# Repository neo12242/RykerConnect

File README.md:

> **Hardware testing status:** I have not tested this project on physical hardware yet. I am still working on my hardware. Software and simulator checks do not establish that the physical hardware works.

# RykerConnect

A motorcycle companion app, ESP32-S3 display system, and hardware-free simulator, based on [JanB97/RykerConnect](https://github.com/JanB97/RykerConnect). This fork brings the Android software expansion and the revised JLCPCB carrier designs together. It is a prototype project, not a validated vehicle accessory.

## What is included

- **Android app:** Dashboard, Bluetooth connection tools, GPS ride recording and summaries, trip maps/replay/charts, photos, fuel and maintenance records, vehicle profiles, themes, home-screen widgets, and local backup/restore.
- **ESP simulator:** A virtual BLE peripheral connected through Android Emulator/netsim, with two browser-rendered OLED panels, settings, sensor controls, failure scenarios, and a guided ride.
- **Firmware:** PlatformIO sources for the revised boards, including the REV05 PCF8563 clock and BME280 sensor support.
- **Hardware:** Native KiCad designs, local libraries, Gerbers, JLCPCB BOM/placement files, wiring instructions, and prototype acceptance procedures.
- **Optional DadRides integration:** Publishing stays built into the Android APK and is disabled by default. The [DadRides website/API](https://github.com/neo12242/DadRides) lives in a separate repository. There is no separate plugin APK, and the app works without the website.

Phone and ESP editions now share ownership spending, modification tracking and service tools. Ride recovery, shared libraries and Wear OS controls are also included; see [current application updates](docs/CURRENT-FEATURES.md). Personal deployment notes, backups, credentials and ride data are excluded from source publication.

## Start here

| Goal | Guide |
|---|---|
| Try the app and virtual displays without electronics | [Simulator setup and use](Simulator/README.md) |
| Build/install the Android app | [Android setup](docs/ANDROID.md) |
| Learn the app's features | [User guide](docs/USER-GUIDE.md) |
| Select a PCB and find the JLCPCB upload files | [Hardware guide](Hardware/README.md) |
| Build firmware | [Firmware guide](Firmware/README.md) |
| Understand this fork's changes and limitations | [Changes](docs/CHANGES.md) |
| Develop from the maintained checkout and run baseline checks | [Development and validation](docs/DEVELOPMENT.md) |
| Configure the optional public ride site | [DadRides](https://github.com/neo12242/DadRides) |

## Visual tour

These development screenshots illustrate the app and simulator. Some show earlier navigation layouts. Demo routes and guided rides are synthetic. Click an image to view it at full size.

| Android dashboard | Trip maps and replay | Simulator sensor controls |
|---|---|---|
|  |  |  |
| Ride information, music, and navigation in one dashboard, with tabs for connection tools, trips, garage, and settings. | Explore a synthetic demonstration ride. The map marks its start and finish, while replay follows the recorded timeline. Gaps remain visible instead of implying continuous GPS coverage. | Toggle virtual sensors and test missing or stale readings. This screen models the earlier DS3231 clock; REV05 hardware uses PCF8563 and requires separate physical testing. |
| [App user guide](docs/USER-GUIDE.md) | [Ride features](docs/USER-GUIDE.md#rides) | [Simulator setup and controls](Simulator/README.md) |

### Try it without hardware

The guided demo previews music, navigation, sensor readings, and ride progress. Playback controls let you start, reset, and change speed without recording a real trip.

See [foldable presentation setup](Simulator/README.md#optional-foldable-presentation).

### REV05C-12V carrier board

KiCad top-layer artwork for the cost-reduced carrier prototype, showing module sockets, battery holder, power circuitry, and peripheral connections. **This is design artwork—not a photograph of assembled or tested hardware.**

See the [hardware guide](Hardware/README.md) for revision selection, matched JLCPCB upload files, separate purchases, and power precautions.

## Quick start: Windows simulator

The first run requires Android Studio/SDK, a Google APIs x86_64 emulator named `RykerConnect_Pixel_7`, Python 3.13, a built debug APK, and the simulator's Python environment. See the [full guide](Simulator/README.md) before running these commands from the repository root:

```powershell
cd Android
.\gradlew.bat assembleCompanionDebug assemblePhoneDebug
cd ..
py -3.13 -m venv Simulator/.venv
.\Simulator\.venv\Scripts\python.exe -m pip install -r Simulator/requirements.txt
& '.\Start RykerConnect Demo.cmd'
```

In the app, open **Connect**, select **RykerConnect-MainUnit**, and pair with the simulator's public test PIN **123456**. The OLED preview opens at <http://127.0.0.1:8876/>. Use **Settings**, **Test scenarios**, and the **I2C test bench** to explore. No physical ESP or Bluetooth dongle is needed for the virtual connection. An intercom is not simulated.

The simulator models protocol/display behavior; it does **not** execute ESP firmware or emulate electrical hardware. Its RTC controls model the earlier DS3231 behavior, while REV05 hardware uses PCF8563. Neither validates the other electrically.

## Hardware status

The latest cost-reduced accessory-power prototype is **REV05C-12V**. **REV05-USB** is a separate USB/regulated-5V option. Use a variant's Gerbers, BOM and CPL together. Do not mix revisions. Read [power selection and bench acceptance](Hardware/REV05C-12V/POWER-AND-TEST.md) before applying power. USB and external power must not be connected together with J8 closed.

JLCPCB placement/model alignment, through-hole assembly acceptance, physical boot, sensor wiring, thermal behavior, enclosure fit and vehicle testing remain pending. Past pricing/stock observations are dated snapshots, not current quotes. The development board, displays, sensor, battery and mating cables are separate purchases.

## Privacy and configuration

The published source excludes local pairing keys, owner keys, SDK paths, app-data backups, ride/receipt exports, logs and development caches. Local setup creates new private files; keep them ignored. Never upload `Simulator/bonds.json`, DadRides `.dev.vars`/`owner-local.txt`, signing keys, or app backups. Backups are not encrypted and may contain locations, vehicle details and original photo metadata.

DadRides uploads only after enabling/configuring the integration and preparing a public copy. Review route trimming and selected photos before publishing. Endpoint trimming is not a guarantee of anonymity. The site does not need a Cloudflare account token in the app.

## Repository layout

`Android/`, `Simulator/`, `Firmware/RykerConnect-REV05/`, and `Hardware/REV05C-12V/` are the current entry points. Older local revisions remain for reference and generation dependencies. Upstream `AndroidApp/`, `Software/`, `Firmware/MainUnit_ESP32S3-REV01/`, `Hardware/KiCad/` and `CAD/` are retained for provenance; their APKs/firmware and enclosure are not the updated release. Build the current source instead.

## Attribution and license

Original project by [JanB97](https://github.com/JanB97), with upstream contributors and notices preserved. This fork retains the upstream [GPL-3.0 license](LICENSE). The [original README](docs/UPSTREAM-README.md) records upstream limitations. Dependencies and vendor documents retain their respective notices and licenses.

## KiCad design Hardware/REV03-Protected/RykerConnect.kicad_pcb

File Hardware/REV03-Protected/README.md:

> Historical revision: see [the hardware index](../README.md) for current options. Physical testing is pending.

# RykerConnect REV03 — protected accessory-input prototype

**Use this revision for the new prototype.** It supersedes the REV02 manufacturing set for the ignition-switched 12V accessory installation. The source Downloads project and the previous REV02 package remain unchanged. This is a completed design/export package; no physical board has been assembled or tested.

## JLCPCB files

Upload these together, without mixing revisions:

1. `manufacturing/Gerbers.zip` — fabrication layers and plated/non-plated drills.
2. `manufacturing/BOM.csv` — **44 fitted components in 31 part groups**, all with LCSC catalog codes.
3. `manufacturing/CPL.csv` — **32 top-side and 12 bottom-side placements**.

Select an assembly service supporting both sides, the through-hole J1 and USB mechanical tabs. J1 is intentionally included in the CPL. Confirm stock, any preorder/Global Sourcing, and actual placement models before ordering. A catalog code is not a stock reservation or assembly acceptance. Use the Gerbers.zip above for fabrication, not the complete delivery archive.

The enclosure must clear the newly populated underside. Reserve roughly 3mm below the PCB for these components and verify the actual enclosure and manufacturer models before fabrication. The board outline and mounting-hole positions are preserved. This revision may cost more to assemble because it uses both sides.

## What changed

The accessory path is now:

**Fused, switched accessory 12V → J1 → transient suppressors/input capacitors → U6 electronic protection → original diode OR-ing → original 3.3V converter.**

- U6, TI **TPS26600PWPR**, adds reverse-input blocking, programmable overvoltage disconnect, startup slew control and approximately 1A overcurrent protection. MODE is open, selecting the auto-retry circuit-breaker behavior; SHDN uses its internal bias.
- R7/R8/R9 form a 120k/20k/10k divider: nominal **17.85V overvoltage cutoff**, **16.5V recovery**, and **5.95V undervoltage startup threshold**. Low voltage during engine cranking can shut the unit down and restart it; uninterrupted crank operation is not claimed.
- R10 is 12k for nominal 1A protection. C16 is 10nF for approximately a 1ms output ramp at 12V. The current limit is a protection threshold, not a new 1A external accessory output.
- D2 **SMBJ33A** and D4 **SMBJ18A** form an asymmetric TVS pair, connected anode-to-anode. The lower negative clamp accounts for the charged output capacitor and the chip's input-to-output voltage limit. Neither diode is the bidirectional `CA` version.
- C14/C17 provide 2uF nominal, 100V-rated input capacitance. C15 adds local output capacitance. D3 **B140-13-F**, cathode to protected output, limits negative output excursions.
- U6's RTN and exposed pad use an **isolated bottom copper island**. They are deliberately not tied to system GND. The custom footprint follows TI's PWP0016A land drawing, with a segmented exposed-pad paste pattern. There are no through-board thermal vias in this island; temperature at the real load must be checked.
- The protection circuit is on the bottom, preserving the original outline and front-side component locations. Two local ground returns were provided, and decorative bottom artwork was moved away from the new circuit. Original author attribution remains.
- The USB input remains behind its original diode OR-ing path. No firmware-controlled power sequencing or new Android feature was required.

## Installation and sensor

the project owner confirmed **ignition-switched accessory 12V** and approximately **one foot / 30cm** of sensor cable. Use a properly fused accessory branch and verify its connector polarity and wire rating. The electronic protection does not protect upstream wiring or a fault in the input TVS itself. Do not replace the vehicle's fuse with a larger value to address a fault. The unit normally powers off with the accessory supply; a connected USB supply can still power it.

Keep the external sensor as an assembled [Adafruit BME280 STEMMA QT module, product 2652](https://www.adafruit.com/product/2652), connected directly to J5 at 100kHz I2C. No extender is fitted for the initial one-foot run. Confirm reliable operation with the actual cable and vehicle electrical loads.

| J5 pin | Signal |
|---|---|
| 1 | GND |
| 2 | +3.3V |
| 3 | SDA, GPIO8 |
| 4 | SCL, GPIO18 |

Use a correctly wired JST SH/STEMMA QT cable. Power off before connection, and never put vehicle 12V or 5V on J5. Locate the sensor away from engine/electronics heat and sunlight, inside a ventilated splash-protected enclosure. Temperature, humidity and absolute pressure are measurements; they remain separate from GPS weather forecasts. A BMP280 is not a humidity-capable replacement.

The battery holder is assembled on the PCB; the CR2032 cell, OLED, external sensor module, cables, media remote and enclosure are separate items. Turnkey PCB assembly does not automatically include these items or firmware programming.

## Validation performed

- KiCad 10.0.6: **zero configured DRC violations, zero unconnected items, zero schematic parity issues, zero ERC violations**. This does not mean all optional KiCad rules were enabled.
- BOM/CPL sets match all 44 fitted components. The source netlist independently confirms that J1 feeds U6, the protected output feeds D1, the TVS diodes share only their anodes, and RTN is separate from GND.
- DC corner calculations include independent pin leakage and resistor tolerances. With 1% resistors the calculated cutoff is 17.20–18.75V. A wider 2.5% resistor-error envelope gives 16.73–19.28V, preserving margin above normal 16V operation and below the existing 25V capacitor rating. These are static calculations, not measured transient overshoot.
- Only new protection nets were imported from local Freerouting output. Existing signal and USB routing were not imported or optimized by that tool. The detailed native checks are the acceptance results; intermediate router logs are diagnostic.
- Original source hashes, board outline and retained component positions are checked. The preserved REV02 software is reused; it was previously built successfully with 32 Android unit tests passing. It was not reflashed or physically retested for this revision.

Reports, native placements, schematic/assembly PDFs, calculations and routing provenance are in `validation`. Purchasing identities and sources are in `selected-parts.json`.

## Prototype acceptance still required

This circuit targets normal 9–16V accessory operation, reverse connection at -16V, overvoltage disconnect for a **suppressed load dump up to 35V**, and short transients within the TVS ratings. It is **not qualified for a full unsuppressed alternator load dump**, and is not an ISO 7637/16750-certified automotive assembly. The protection chip is an industrial-rated part. Actual temperature, pulse energy, source impedance, DC-bias capacitance and PCB overshoot must be tested.

Before committing an assembly order, review:

1. JLCPCB stock/process acceptance and model alignment for every part, especially U6/D2/D3/D4 and the bottom-side rotation convention. U6 pin 1 must agree with the board marker. D2/D4 cathode polarity is essential.
2. J1/J2 mechanical fit, the exact SOG320132A OLED variant, and underside/enclosure clearance.
3. The actual accessory branch fuse and cable ratings.

Then test the assembled prototype on a protected, current-limited bench supply before connecting it to the vehicle:

1. Inspect soldering, isolated RTN, polarity and input/3.3V continuity.
2. Verify normal supply startup, soft start, overvoltage disconnect/recovery and undervoltage behavior. Apply controlled reverse-polarity tests with current limiting and no alternate grounded cables that could bypass the test path.
3. Verify overload/short-circuit auto-retry and temperature at the intended load. Recheck the regulator's local ground return.
4. Test the specified transient waveforms with suitable equipment; verify voltage at both U6 and the downstream converter, not just at J1.
5. Verify the OLED, USB, Bluetooth, RTC and environmental readings; confirm unavailable/stale readings and recovery. Finally test engine-start and vehicle electrical-noise behavior.

## Placement conventions and software

CPL coordinates share the KiCad auxiliary origin on both sides. Existing assembler adjustments are retained: J1 centroid offset (-1.5mm X, -2.53mm Y), U1 rotation +180 degrees and U2 rotation -90 degrees. New bottom parts use the native KiCad orientation as the model-preview starting point. These are not a substitute for JLCPCB's actual placement preview. DNP C1/C2/JP1 and off-board Q1 stay excluded; test pads, mounting holes and artwork stay excluded.

The included `software` files are the previously built REV02/N8 firmware and Android debug APK, reused unchanged because GPIOs, memory variant and sensor protocol are unchanged. Use the `RykerConnect_REV02` PlatformIO environment from the included firmware source for a complete first-board upload. `firmware.bin` alone is only the application image; do not flash it at address zero. The APK is not installed by this package. Earlier simulator-only trip/navigation/weather display extensions remain separate from this physical firmware.

## Rebuild

Keep this directory beside `REV02-Corrected`, which is the preserved input. Run `build_schematic.py` with regular Python, then `build_board.py`, `import_routing.py` and `finish_board.py` with KiCad's bundled Python; run `check_calculations.py` and `export_release.py` with regular Python. Run `finish_board.py` once per fresh board build. The saved `validation/protection.ses` supplies the reviewed routing, so reproducing the delivered design does not require downloading an autorouter.

For intentional rerouting, `prepare_routing.py` fixes existing routes in DSN and defines new net widths. Local Freerouting 2.4.1 was run with analytics, GUI, server, fanout and optimizer disabled. `import_routing.py` imports only the eight protection nets and rejects component movements by ignoring placement data. Reinspect and revalidate any rerouted result; the current finishing adjustments apply to the delivered geometry only.

References: [TI TPS2660 datasheet and reference circuit](https://www.ti.com/lit/ds/symlink/tps2660.pdf), [Littelfuse SMBJ datasheet](https://m.littelfuse.com/~/media/electronics/datasheets/tvs_diodes/littelfuse_tvs_diode_smbj_datasheet.pdf.pdf), [Freerouting CLI](https://github.com/freerouting/freerouting/blob/v2.4.1/docs/command_line_arguments.md). Per-part catalog links are recorded with the BOM identities.

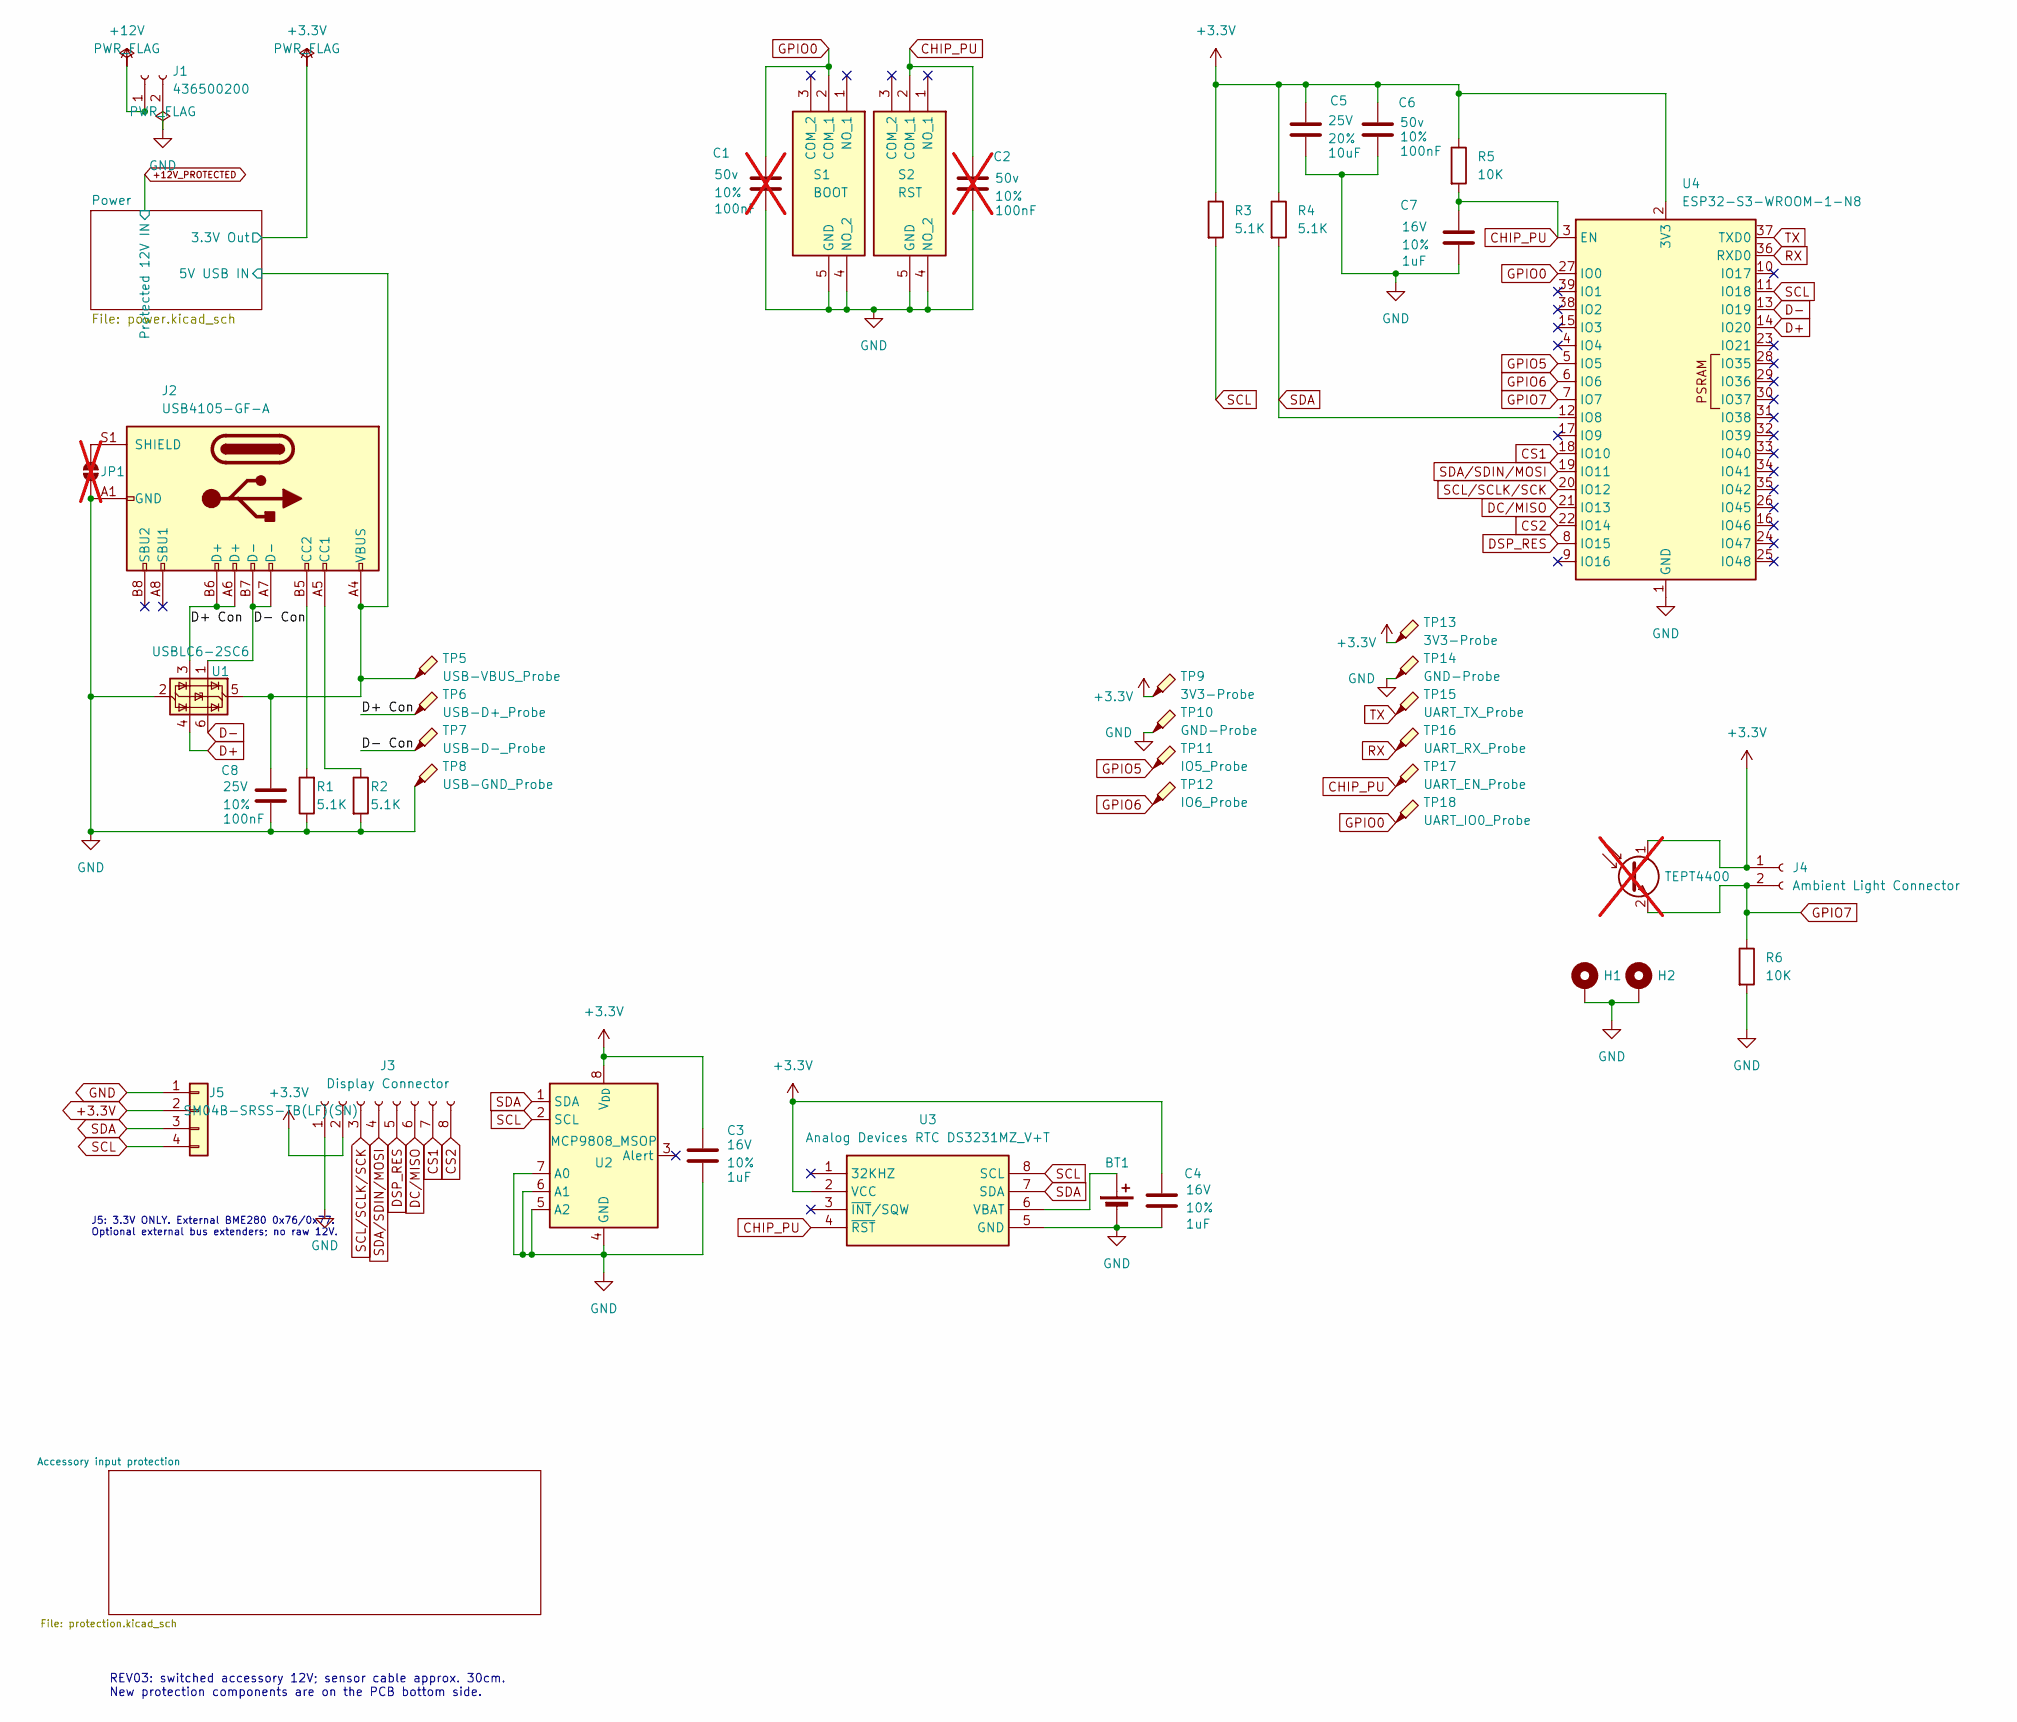
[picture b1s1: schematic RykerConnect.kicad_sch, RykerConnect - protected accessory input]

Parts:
BT1: Holders Linx CR2032; BT1_BATHLD001; MPN BAT-HLD-001; LCSC C7501066
C1: 100nF; C1_C_0603_1608Metric_Pad1.08x0.95mm_HandSolder; Voltage 50v; Tolerance 10%; not fitted
C2: 100nF; C2_C_0603_1608Metric_Pad1.08x0.95mm_HandSolder; Voltage 50v; Tolerance 10%; not fitted
C3: 1uF; C3_C_0603_1608Metric_Pad1.08x0.95mm_HandSolder; Voltage 16V; Tolerance 10%; MPN CL10B105KO8NNNC; LCSC C59782
C4: 1uF; C4_C_0603_1608Metric_Pad1.08x0.95mm_HandSolder; Voltage 16V; Tolerance 10%; MPN CL10B105KO8NNNC; LCSC C59782
C5: 10uF; C5_C_0603_1608Metric_Pad1.08x0.95mm_HandSolder; Voltage 25V; Tolerance 20%; MPN C1608X5R1E106M080AC; LCSC C2168289
C6: 100nF; C6_C_0603_1608Metric_Pad1.08x0.95mm_HandSolder; Voltage 50v; Tolerance 10%; MPN C0603C104K5RAC7082; LCSC C1882722
C7: 1uF; C7_C_0603_1608Metric_Pad1.08x0.95mm_HandSolder; Voltage 16V; Tolerance 10%; MPN CL10B105KO8NNNC; LCSC C59782
C8: 100nF; C8_C_0603_1608Metric_Pad1.08x0.95mm_HandSolder; Voltage 25V; Tolerance 10%; MPN C0603C104K3RACTU; LCSC C2167527
H1: MountingHole_Pad; H1_MountingHole_2.2mm_M2_ISO14580_Pad_TopBottom
H2: MountingHole_Pad; H2_MountingHole_2.2mm_M2_ISO14580_Pad_TopBottom
J1: 436500200; J1_43650-02_00,01,02_; MPN 436500200; LCSC C192562
J2: USB4105-GF-A; J2_USB_C_Receptacle_GCT_USB4105-xx-A_16P_TopMnt_Horizontal; MPN USB4105-GF-A; LCSC C3020560
J3: Display Connector; J3_JST_SH_SM08B-SRSS-TB_1x08-1MP_P1.00mm_Horizontal; MPN SM08B-SRSS-TB(LF)(SN); LCSC C160407
J4: Ambient Light Connector; J4_JST_SH_SM02B-SRSS-TB_1x02-1MP_P1.00mm_Horizontal; MPN SM02B-SRSS-TB(LF)(SN); LCSC C160402
J5: SM04B-SRSS-TB(LF)(SN); J5_JST_SH_SM04B-SRSS-TB_1x04-1MP_P1.00mm_Horizontal; MPN SM04B-SRSS-TB(LF)(SN); LCSC C160404
JP1: SolderJumper_2_Open; JP1_R_0603_1608Metric_Pad0.98x0.95mm_HandSolder; not fitted
Q1: TEPT4400; LED_D3.0mm_Clear; not fitted
R1: 5.1K; R1_R_0805_2012Metric_Pad1.20x1.40mm_HandSolder; MPN RS73F2ARTTD5101D; LCSC C5890991
R2: 5.1K; R2_R_0805_2012Metric_Pad1.20x1.40mm_HandSolder; MPN RS73F2ARTTD5101D; LCSC C5890991
R3: 5.1K; R3_R_0805_2012Metric_Pad1.20x1.40mm_HandSolder; MPN RS73F2ARTTD5101D; LCSC C5890991
R4: 5.1K; R4_R_0805_2012Metric_Pad1.20x1.40mm_HandSolder; MPN RS73F2ARTTD5101D; LCSC C5890991
R5: 10K; R5_R_0805_2012Metric_Pad1.20x1.40mm_HandSolder; Tolerance 1%; MPN CRGP0805F10K; LCSC C2074940
R6: 10K; R6_R_0805_2012Metric_Pad1.20x1.40mm_HandSolder; MPN CRGP0805F10K; LCSC C2074940
S1: BOOT; S1_435451019820; Mouser Part Number 710-435451019820
S2: RST; S2_435451019820; Mouser Part Number 710-435451019820
TP5: USB-VBUS_Probe; TP5_TestPoint_Pad_D1.0mm
TP6: USB-D+_Probe; TP6_TestPoint_Pad_D1.0mm
TP7: USB-D-_Probe; TP7_TestPoint_Pad_D1.0mm
TP8: USB-GND_Probe; TP8_TestPoint_Pad_D1.0mm
TP9: 3V3-Probe; TP9_TestPoint_Pad_D2.0mm
TP10: GND-Probe; TP10_TestPoint_Pad_D2.0mm
TP11: IO5_Probe; TP11_TestPoint_Pad_D2.0mm
TP12: IO6_Probe; TP12_TestPoint_Pad_D2.0mm
TP13: 3V3-Probe; TP13_TestPoint_Pad_D1.5mm
TP14: GND-Probe; TP14_TestPoint_Pad_D1.5mm
TP15: UART_TX_Probe; TP15_TestPoint_Pad_D1.5mm
TP16: UART_RX_Probe; TP16_TestPoint_Pad_D1.5mm
TP17: UART_EN_Probe; TP17_TestPoint_Pad_D1.5mm
TP18: UART_IO0_Probe; TP18_TestPoint_Pad_D1.5mm
U1: USBLC6-2SC6; U1_SOT-23-6; MPN USBLC6-2SC6; LCSC C7519
U2: MCP9808_MSOP; U2_MSOP-8_3x3mm_P0.65mm; MPN MCP9808T-E/MS; LCSC C129490
U3: Analog Devices RTC DS3231MZ_V+T; U3_SOIC127P600X175-8N; Mouser Part Number 700-DS3231MZ/V+T
U4: ESP32-S3-WROOM-1-N8; U4_ESP32-S3-WROOM-1; MPN ESP32-S3-WROOM-1-N8; LCSC C2913198

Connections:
+3.3V: C3.1, C4.1, C5.1, C6.1, J3.2, J4.1, J5.2, Q1.1 (C), R3.1, R4.1, R5.1, TP9.1 (1_1), TP13.1 (1_1), U2.8 (V_{DD}), U3.2 (VCC), U4.2 (3V3); also elsewhere on the board
+12V: J1.1; also elsewhere on the board
/D+ Con: J2.A6 (D+), J2.B6 (D+), TP6.1 (1_1), U1.3 (I/O2)
/D- Con: J2.A7 (D-), J2.B7 (D-), TP7.1 (1_1), U1.1 (I/O1)
/Power/5V USB IN: C8.1, J2.A4 (VBUS), J2.A9 (VBUS), J2.B4 (VBUS), J2.B9 (VBUS), TP5.1 (1_1), U1.5 (VBUS); also elsewhere on the board
CHIP_PU: C2.1, C7.1, R5.2, S2.2 (COM_1), TP17.1 (1_1), U3.4 (~RST), U4.3 (EN)
CS1: J3.7, U4.18 (IO10)
CS2: J3.8, U4.22 (IO14)
D+: U1.4 (I/O2), U4.14 (IO20)
D-: U1.6 (I/O1), U4.13 (IO19)
DC/MISO: J3.6, U4.21 (IO13)
DSP_RES: J3.5, U4.8 (IO15)
GND: BT1.2 (-), C1.2, C2.2, C3.2, C4.2, C5.2, C6.2, C7.2, C8.2, H1.1 (1_1), H2.1 (1_1), J1.2, J2.A1 (GND), J2.A12 (GND), J2.B1 (GND), J2.B12 (GND), J3.1, J5.1, J5.MP (Mounting anchors), JP1.1 (A), R1.1, R2.2, R6.2, S1.4 (NO_2), S1.5 (GND), S2.4 (NO_2), S2.5 (GND), TP8.1 (1_1), TP10.1 (1_1), TP14.1 (1_1), U1.2 (GND), U2.4 (GND), U2.5 (A2), U2.6 (A1), U2.7 (A0), U3.5 (GND), U4.1 (GND), U4.40 (GND); also elsewhere on the board
GPIO0: C1.1, S1.2 (COM_1), TP18.1 (1_1), U4.27 (IO0)
GPIO5: TP11.1 (1_1), U4.5 (IO5)
GPIO6: TP12.1 (1_1), U4.6 (IO6)
GPIO7: J4.2, Q1.2 (E), R6.1, U4.7 (IO7)
unnamed: BT1.1 (+), U3.6 (VBAT)
unnamed: J2.A5 (CC1), R2.1
unnamed: J2.B5 (CC2), R1.2
unnamed: J2.S1 (SHIELD), JP1.2 (B)
RX: TP16.1 (1_1), U4.36 (RXD0)
SCL: J5.4, R3.2, U2.2 (SCL), U3.8 (SCL), U4.11 (IO18)
SCL/SCLK/SCK: J3.3, U4.20 (IO12)
SDA: J5.3, R4.2, U2.1 (SDA), U3.7 (SDA), U4.12 (IO8)
SDA/SDIN/MOSI: J3.4, U4.19 (IO11)
TX: TP15.1 (1_1), U4.37 (TXD0)

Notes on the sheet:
J5: 3.3V ONLY. External BME280 0x76/0x77. Optional external bus extenders; no raw 12V.
REV03: switched accessory 12V; sensor cable approx. 30cm. New protection components are on the PCB bottom side.

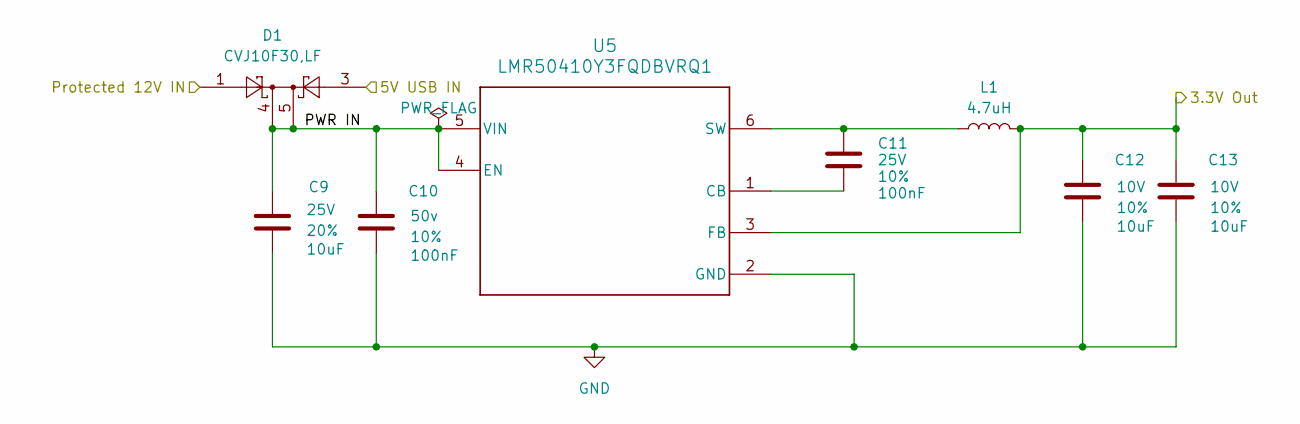
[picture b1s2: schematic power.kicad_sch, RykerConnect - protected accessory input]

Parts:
C9: 10uF; C9_C_0603_1608Metric_Pad1.08x0.95mm_HandSolder; Voltage 25V; Tolerance 20%; MPN C1608X5R1E106M080AC; LCSC C2168289
C10: 100nF; C10_C_0603_1608Metric_Pad1.08x0.95mm_HandSolder; Voltage 50v; Tolerance 10%; MPN C0603C104K5RAC7082; LCSC C1882722
C11: 100nF; C11_C_0603_1608Metric_Pad1.08x0.95mm_HandSolder; Voltage 25V; Tolerance 10%; MPN C0603C104K3RACTU; LCSC C2167527
C12: 10uF; C12_C_0805_2012Metric_Pad1.18x1.45mm_HandSolder; Voltage 10V; Tolerance 10%; MPN C0805C106K8PACTU; LCSC C2167673
C13: 10uF; C13_C_0805_2012Metric_Pad1.18x1.45mm_HandSolder; Voltage 10V; Tolerance 10%; MPN C0805C106K8PACTU; LCSC C2167673
D1: CVJ10F30,LF; D1_SOTFL65P210X75-5N; MPN CVJ10F30,LF; LCSC C5609371
L1: 4.7uH; L1_INDPM5653X430N; MPN 744316470; LCSC C2651181
U5: LMR50410Y3FQDBVRQ1; U5_DBV0006A-IPC_A; MPN LMR50410Y3FQDBVRQ1; LCSC C5219374

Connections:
+3.3V: C12.1, C13.1, L1.2, U5.3 (FB); also elsewhere on the board
+12V_PROTECTED: D1.1; also elsewhere on the board
/Power/5V USB IN: D1.3; also elsewhere on the board
/Power/PWR IN: C9.1, C10.1, D1.4, D1.5, U5.4 (EN), U5.5 (VIN)
GND: C9.2, C10.2, C12.2, C13.2, U5.2 (GND); also elsewhere on the board
unnamed: C11.2, U5.1 (CB)
unnamed: C11.1, L1.1, U5.6 (SW)

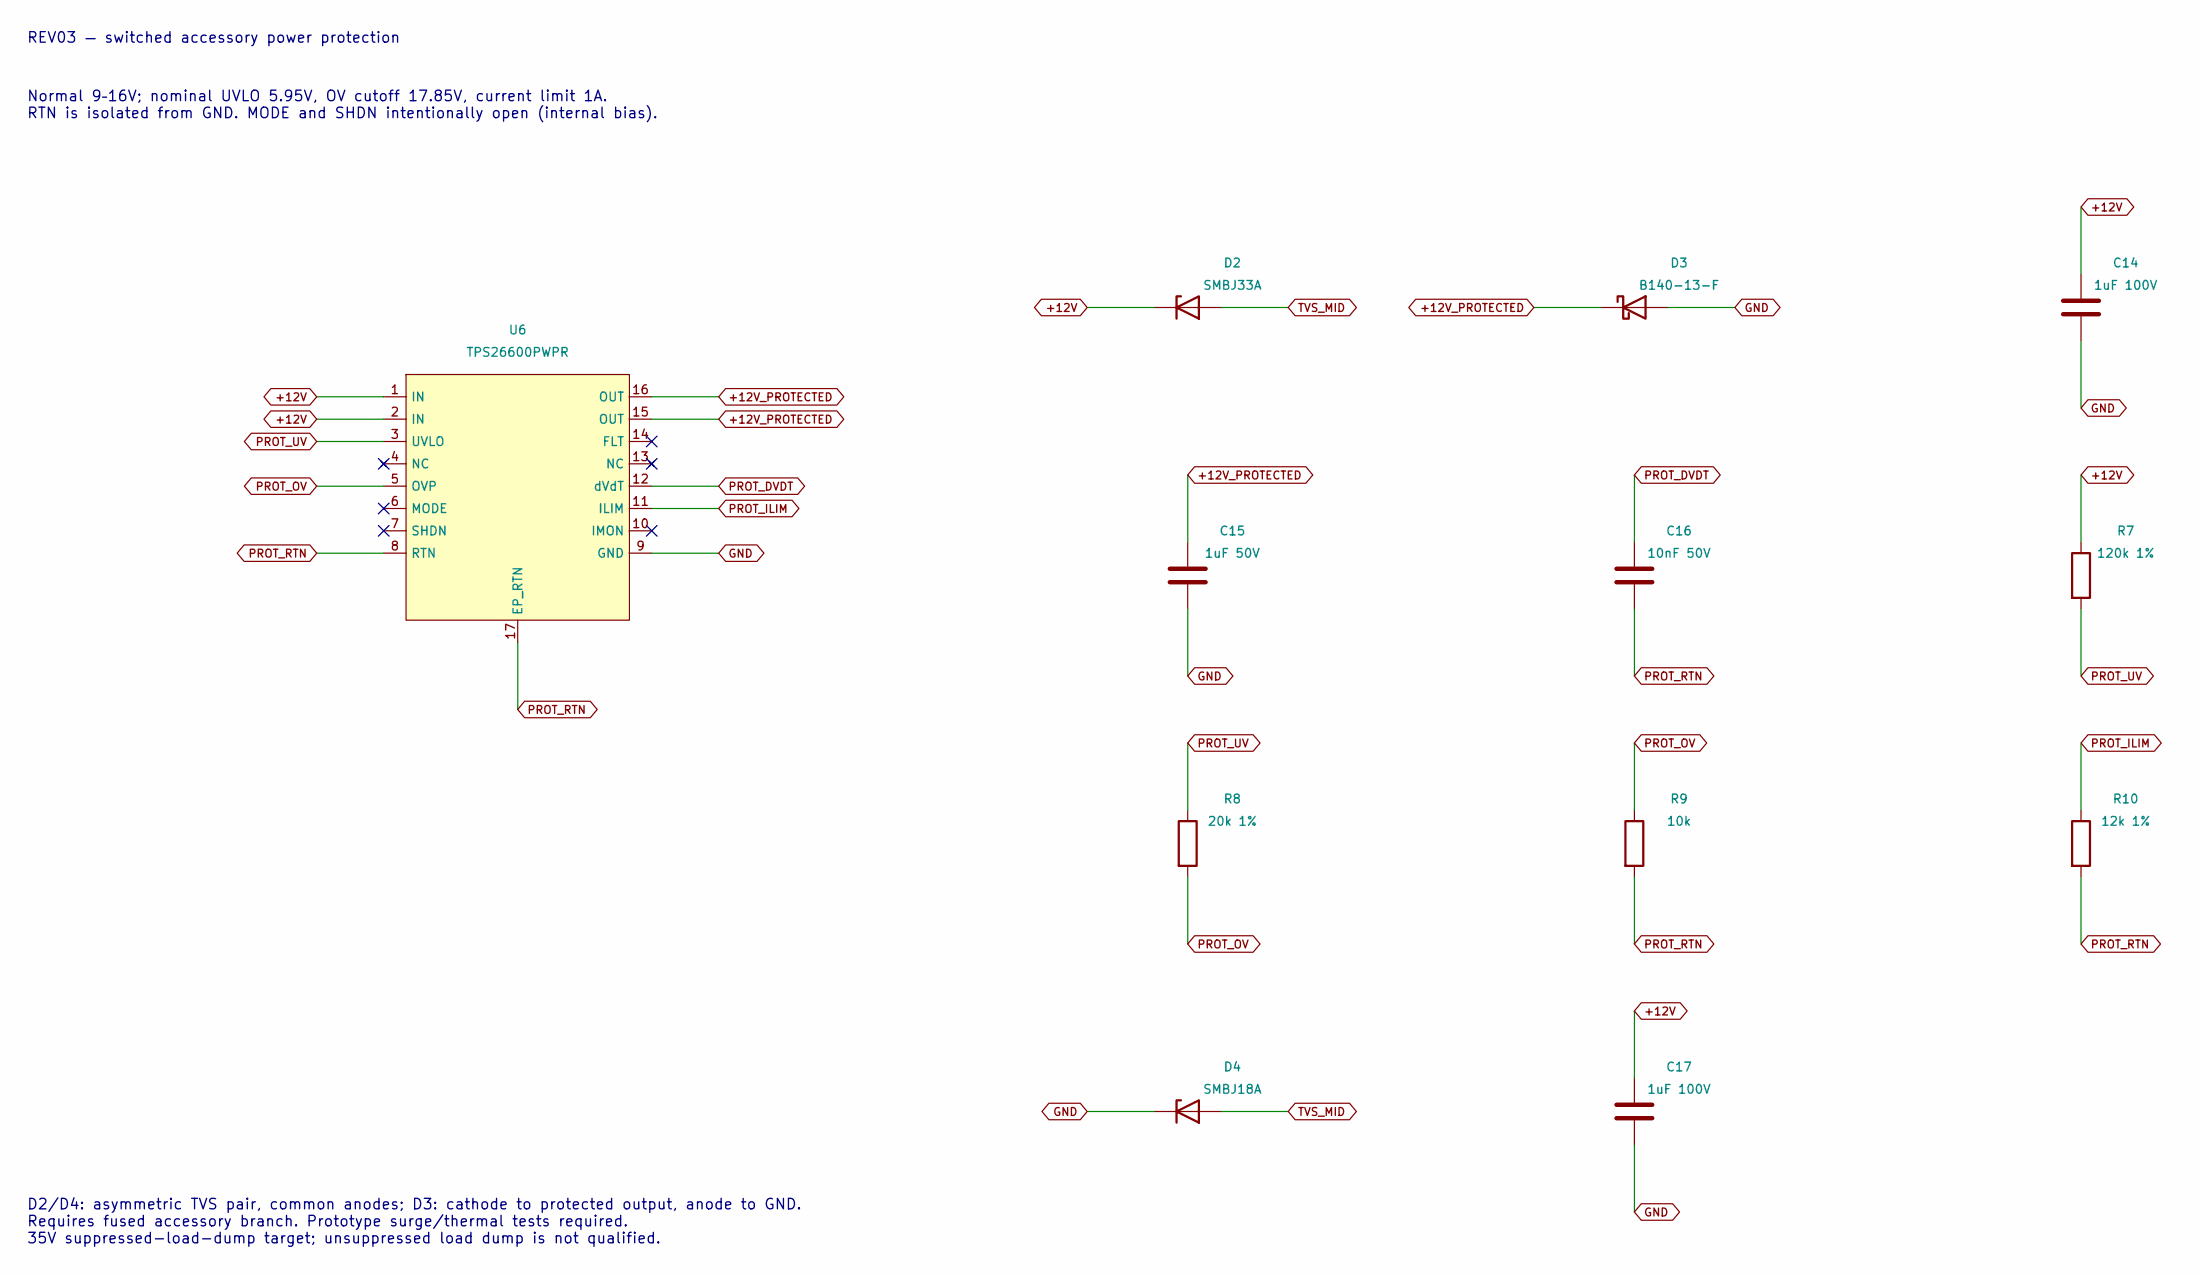
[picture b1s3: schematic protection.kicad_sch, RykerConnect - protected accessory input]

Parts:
C14: 1uF 100V; C14_C_1206_3216Metric; MPN CL31B105KCHNNNE; LCSC C13832
C15: 1uF 50V; C15_C_0805_2012Metric; MPN CL21B105KBFNNNE; LCSC C28323
C16: 10nF 50V; C16_C_0603_1608Metric; MPN CL10B103KB8NNNC; LCSC C1589
C17: 1uF 100V; C17_C_1206_3216Metric; MPN CL31B105KCHNNNE; LCSC C13832
D2: SMBJ33A; D2_D_SMB; MPN SMBJ33A; LCSC C224019
D3: B140-13-F; D3_D_SMA; MPN B140-13-F; LCSC C15759
D4: SMBJ18A; D4_D_SMB; MPN SMBJ18A; LCSC C151256
R7: 120k 1%; R7_R_0603_1608Metric; MPN RC0603FR-07120KL; LCSC C114607
R8: 20k 1%; R8_R_0603_1608Metric; MPN RC0603FR-0720KL; LCSC C105575
R9: 10k; R9_R_0805_2012Metric; MPN CRGP0805F10K; LCSC C2074940
R10: 12k 1%; R10_R_0603_1608Metric; MPN RC0603FR-0712KL; LCSC C114659
U6: TPS26600PWPR; U6_Protection_HTSSOP16_PWP0016A; MPN TPS26600PWPR; LCSC C544399

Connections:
+12V: C14.1, C17.1, D2.1 (K), R7.1, U6.1 (IN), U6.2 (IN); also elsewhere on the board
+12V_PROTECTED: C15.1, D3.1 (K), U6.15 (OUT), U6.16 (OUT); also elsewhere on the board
GND: C14.2, C15.2, C17.2, D3.2 (A), D4.1 (K), U6.9 (GND); also elsewhere on the board
PROT_DVDT: C16.1, U6.12 (dVdT)
PROT_ILIM: R10.1, U6.11 (ILIM)
PROT_OV: R8.2, R9.1, U6.5 (OVP)
PROT_RTN: C16.2, R9.2, R10.2, U6.8 (RTN), U6.17 (EP_RTN)
PROT_UV: R7.2, R8.1, U6.3 (UVLO)
TVS_MID: D2.2 (A), D4.2 (A)

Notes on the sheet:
REV03 — switched accessory power protection
Normal 9–16V; nominal UVLO 5.95V, OV cutoff 17.85V, current limit 1A. RTN is isolated from GND. MODE and SHDN intentionally open (internal bias).
D2/D4: asymmetric TVS pair, common anodes; D3: cathode to protected output, anode to GND. Requires fused accessory branch. Prototype surge/thermal tests required. 35V suppressed-load-dump target; unsuppressed load dump is not qualified.

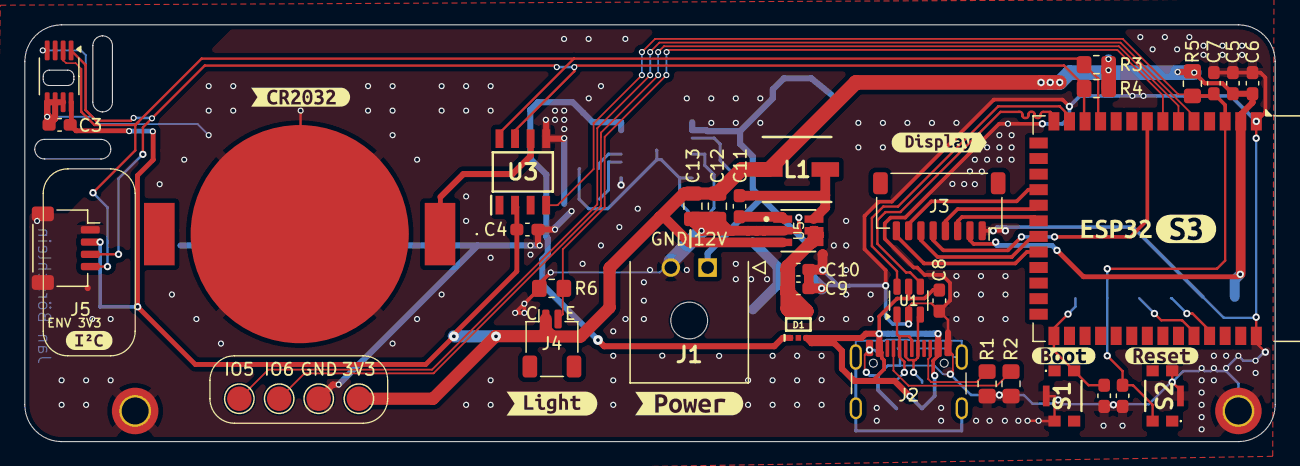
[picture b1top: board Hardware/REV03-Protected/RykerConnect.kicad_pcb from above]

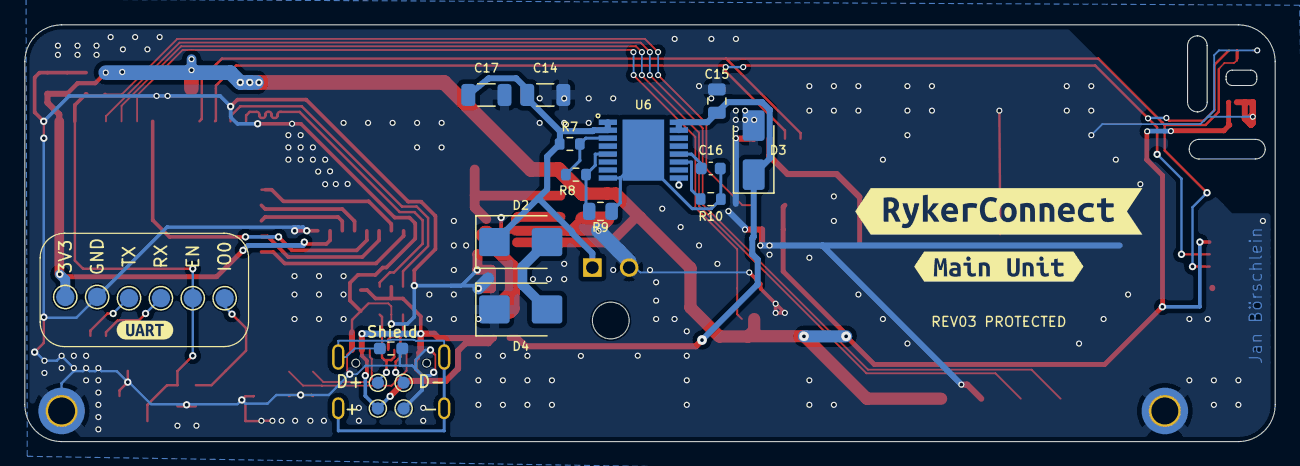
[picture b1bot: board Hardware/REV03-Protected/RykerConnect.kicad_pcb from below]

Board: 2 copper layers, 102.0 x 34.0 mm, 75 parts (27 on the bottom side), 37 nets.

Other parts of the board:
kibuzzard-66281C1F: G***; kibuzzard-66281C1F
kibuzzard-66281DA5: G***; kibuzzard-66281DA5
kibuzzard-66281FA1: G***; kibuzzard-66281FA1
kibuzzard-66282B71: G***; kibuzzard-66282B71
kibuzzard-66296C5A: G***; kibuzzard-66296C5A
kibuzzard-662805BB: G***; kibuzzard-662805BB
kibuzzard-662805C3: G***; kibuzzard-662805C3
kibuzzard-6628061E: G***; kibuzzard-6628061E
kibuzzard-6628064B: G***; kibuzzard-6628064B
kibuzzard-6628065E: G***; kibuzzard-6628065E
kibuzzard-66280634: G***; kibuzzard-66280634
kibuzzard-66281340: G***; kibuzzard-66281340

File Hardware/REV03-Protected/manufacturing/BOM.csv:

Comment,Designator,Footprint,LCSC Part #,Quantity,Manufacturer,Manufacturer Part Number
BAT-HLD-001; Holders Linx CR2032,BT1,BATHLD001,C7501066,1,TE Connectivity / Linx,BAT-HLD-001
CL10B105KO8NNNC; 1uF,"C3,C4,C7",C_0603_1608Metric_Pad1.08x0.95mm_HandSolder,C59782,3,Samsung Electro-Mechanics,CL10B105KO8NNNC
C1608X5R1E106M080AC; 10uF,"C5,C9",C_0603_1608Metric_Pad1.08x0.95mm_HandSolder,C2168289,2,TDK,C1608X5R1E106M080AC
C0603C104K5RAC7082; 100nF,"C6,C10",C_0603_1608Metric_Pad1.08x0.95mm_HandSolder,C1882722,2,KEMET,C0603C104K5RAC7082
C0603C104K3RACTU; 100nF,"C8,C11",C_0603_1608Metric_Pad1.08x0.95mm_HandSolder,C2167527,2,KEMET,C0603C104K3RACTU
C0805C106K8PACTU; 10uF,"C12,C13",C_0805_2012Metric_Pad1.18x1.45mm_HandSolder,C2167673,2,KEMET,C0805C106K8PACTU
"CVJ10F30,LF; CVJ10F30,LF",D1,SOTFL65P210X75-5N,C5609371,1,Toshiba,"CVJ10F30,LF"
436500200; 436500200,J1,"43650-02_00,01,02_",C192562,1,Molex,436500200
USB4105-GF-A; USB4105-GF-A,J2,USB_C_Receptacle_GCT_USB4105-xx-A_16P_TopMnt_Horizontal,C3020560,1,GCT,USB4105-GF-A
SM08B-SRSS-TB(LF)(SN); Display Connector,J3,JST_SH_SM08B-SRSS-TB_1x08-1MP_P1.00mm_Horizontal,C160407,1,JST,SM08B-SRSS-TB(LF)(SN)
SM02B-SRSS-TB(LF)(SN); Ambient Light Connector,J4,JST_SH_SM02B-SRSS-TB_1x02-1MP_P1.00mm_Horizontal,C160402,1,JST,SM02B-SRSS-TB(LF)(SN)
744316470; 4.7uH,L1,INDPM5653X430N,C2651181,1,Wurth Elektronik,744316470
RS73F2ARTTD5101D; 5.1K,"R1,R2,R3,R4",R_0805_2012Metric_Pad1.20x1.40mm_HandSolder,C5890991,4,KOA Speer,RS73F2ARTTD5101D
CRGP0805F10K; 10K,"R5,R6,R9",0805,C2074940,3,TE Connectivity,CRGP0805F10K
435451019820; BOOT,"S1,S2",435451019820,C7464054,2,Wurth Elektronik,435451019820
USBLC6-2SC6; USBLC6-2SC6,U1,SOT-23-6,C7519,1,STMicroelectronics,USBLC6-2SC6
MCP9808T-E/MS; MCP9808_MSOP,U2,MSOP-8_3x3mm_P0.65mm,C129490,1,Microchip,MCP9808T-E/MS
DS3231MZ/V+T; Analog Devices RTC DS3231MZ_V+T,U3,SOIC127P600X175-8N,C3304429,1,Analog Devices / Maxim,DS3231MZ/V+T
ESP32-S3-WROOM-1-N8; ESP32-S3-WROOM-1-N8,U4,ESP32-S3-WROOM-1,C2913198,1,Espressif Systems,ESP32-S3-WROOM-1-N8
LMR50410Y3FQDBVRQ1; LMR50410Y3FQDBVRQ1,U5,DBV0006A-IPC_A,C5219374,1,Texas Instruments,LMR50410Y3FQDBVRQ1
SM04B-SRSS-TB(LF)(SN); SM04B-SRSS-TB(LF)(SN),J5,JST_SH_SM04B-SRSS-TB_1x04-1MP_P1.00mm_Horizontal,C160404,1,JST,SM04B-SRSS-TB(LF)(SN)
TPS26600PWPR; TPS26600PWPR,U6,Protection_HTSSOP16_PWP0016A,C544399,1,Texas Instruments,TPS26600PWPR
SMBJ33A; SMBJ33A,D2,D_SMB,C224019,1,Littelfuse,SMBJ33A
B140-13-F; B140-13-F,D3,D_SMA,C15759,1,Diodes Incorporated,B140-13-F
CL31B105KCHNNNE; 1uF 100V,"C14,C17",C_1206_3216Metric,C13832,2,Samsung Electro-Mechanics,CL31B105KCHNNNE
CL21B105KBFNNNE; 1uF 50V,C15,C_0805_2012Metric,C28323,1,Samsung Electro-Mechanics,CL21B105KBFNNNE
CL10B103KB8NNNC; 10nF 50V,C16,C_0603_1608Metric,C1589,1,Samsung Electro-Mechanics,CL10B103KB8NNNC
RC0603FR-07120KL; 120k 1%,R7,R_0603_1608Metric,C114607,1,Yageo,RC0603FR-07120KL
RC0603FR-0720KL; 20k 1%,R8,R_0603_1608Metric,C105575,1,Yageo,RC0603FR-0720KL
RC0603FR-0712KL; 12k 1%,R10,R_0603_1608Metric,C114659,1,Yageo,RC0603FR-0712KL
SMBJ18A; SMBJ18A,D4,D_SMB,C151256,1,Littelfuse,SMBJ18A
